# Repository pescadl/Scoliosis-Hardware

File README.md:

# Scoliosis-Hardware
Senior Design Project
with launchpad

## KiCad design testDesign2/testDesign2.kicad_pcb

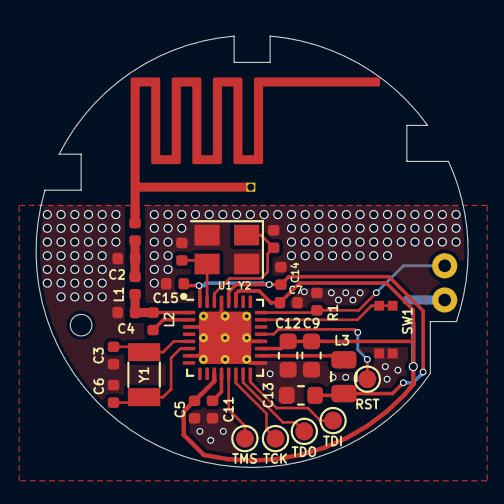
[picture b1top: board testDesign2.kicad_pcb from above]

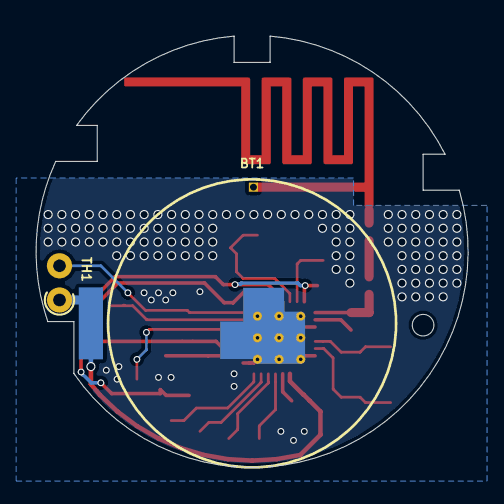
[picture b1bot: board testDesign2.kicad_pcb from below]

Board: 2 copper layers, 24.0 x 24.0 mm, 32 parts (2 on the bottom side), 20 nets.

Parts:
AE1: Antenna; TestDesign2_Antenna
BT1: Battery_Cell; BatteryHolder_Keystone_120_118_CR1616
C1, C3, C6: 12pF; C_0402_1005Metric
C2, C4: 1.2pF; C_0402_1005Metric
C5, C7, C14, C15: 100nF; C_0402_1005Metric
C8, C10: 9pF; C_0402_1005Metric
C9, C13: 10uF; C_0603_1608Metric
C11: 1uF; C_0402_1005Metric
C12: 100nF; C_0603_1608Metric
H1: MountingHole; MountingHole_1.2mm_M1
L1: 2nH; L_0402_1005Metric
L2: 15nH; L_0402_1005Metric
L3: 10uH; L_0805_2012Metric
R1: 51k; R_0402_1005Metric
RST: TP; TestPoint_Pad_D1.0mm
SW1: SW_Push; Switch_EVP-BB4A9B000
TCK: TP; TestPoint_Pad_D1.0mm
TDI: TP; TestPoint_Pad_D1.0mm
TDO: TP; TestPoint_Pad_D1.0mm
TH1: Thermistor; R_Axial_DIN0204_L3.6mm_D1.6mm_P1.90mm_Vertical
TMS: TP; TestPoint_Pad_D1.0mm
U1: CC2640R2FRSM; QFN-32-1EP_4x4mm_P0.4mm_EP2.9x2.9mm_ThermalVias
Y1: 32.768kHz; Crystal_SMD_3215-2Pin_3.2x1.5mm
Y2: 24MHz; Crystal_SMD_SeikoEpson_TSX3225-4Pin_3.2x2.5mm

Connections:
ADC0: R1.1, TH1.2, U1.24
Button: SW1.1, U1.23
DCDC_SW: L3.1, U1.18
GND: BT1.2, C2.2, C3.2, C4.2, C5.2, C6.2, C7.2, C8.2, C9.2, C10.2, C11.2, C12.2, C13.2, C14.2, C15.2, R1.2, SW1.2, U1.3, U1.7, U1.17, U1.20, U1.29, U1.33, Y2.2, Y2.4
unnamed: AE1.1, C1.1
unnamed: C1.2, C2.1, L1.1
unnamed: C3.1, U1.5, Y1.1
unnamed: C4.1, L1.2, L2.1, U1.1
unnamed: C6.1, U1.6, Y1.2
unnamed: C8.1, U1.31, Y2.3
unnamed: C10.1, U1.30, Y2.1
unnamed: C11.1, U1.12
unnamed: L2.2, U1.2
unnamed: TMS.1, U1.13
unnamed: TCK.1, U1.14
unnamed: TDO.1, U1.15
unnamed: TDI.1, U1.16
unnamed: RST.1, U1.21
VDDR: C13.1, C14.1, C15.1, L3.2, U1.28, U1.32
VDDS: BT1.1, C5.1, C7.1, C9.1, C12.1, TH1.1, U1.11, U1.19, U1.27

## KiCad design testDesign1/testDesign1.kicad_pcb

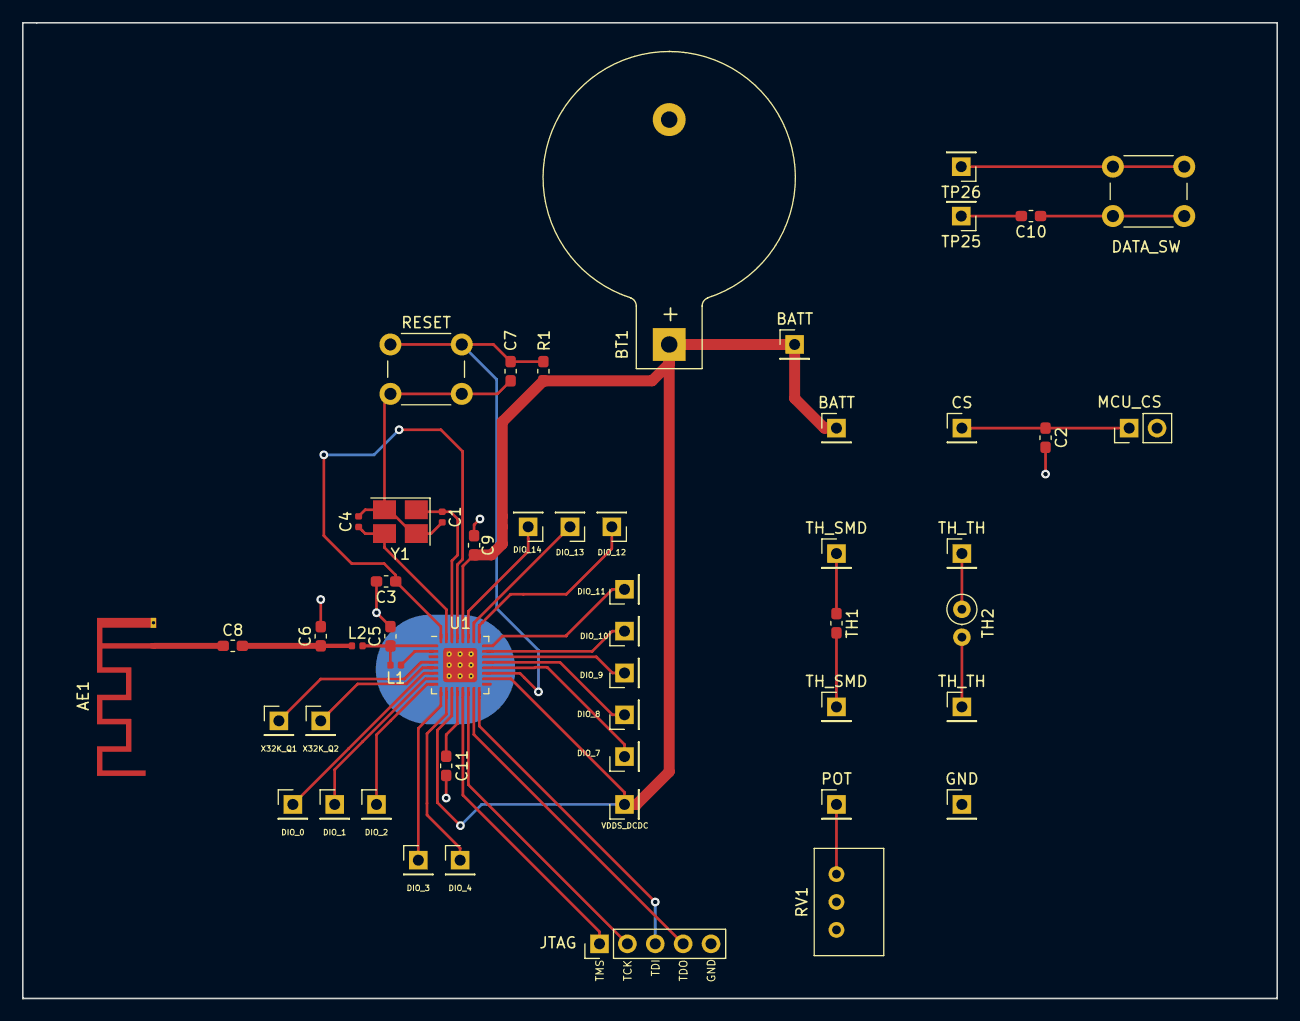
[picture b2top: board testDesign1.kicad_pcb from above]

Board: 2 copper layers, 114.3 x 88.9 mm, 52 parts (0 on the bottom side), 39 nets.

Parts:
AE1: Antenna; Texas_SWRA117D_2.4GHz_Left
BATT: TestPoint; PinHeader_1x01_P2.54mm_Vertical
BATT#2: TestPoint; PinHeader_1x01_P2.54mm_Vertical
BT1: Battery_Cell; BatteryHolder_Keystone_103_1x20mm
C1, C4: 9pF; C_0402_1005Metric
C2: 1nF; C_0603_1608Metric_Pad1.05x0.95mm_HandSolder
C3, C9: 10uF; C_0603_1608Metric_Pad1.05x0.95mm_HandSolder
C5, C6: 1.2pF; C_0603_1608Metric_Pad1.05x0.95mm_HandSolder
C7, C10: 100nF; C_0603_1608Metric_Pad1.05x0.95mm_HandSolder
C8: 12pF; C_0603_1608Metric_Pad1.05x0.95mm_HandSolder
C11: 1uF; C_0603_1608Metric_Pad1.05x0.95mm_HandSolder
CS: TestPoint; PinHeader_1x01_P2.54mm_Vertical
DATA_SW: SW_Push; SW_PUSH_6mm
DIO_0, DIO_1, DIO_2, DIO_3, DIO_4, DIO_7, DIO_8, DIO_9, DIO_10, DIO_11, DIO_12, DIO_13, DIO_14: TestPoint; PinHeader_1x01_P2.54mm_Vertical
GND: TestPoint; PinHeader_1x01_P2.54mm_Vertical
JTAG: Conn_01x05_Male; PinHeader_1x05_P2.54mm_Vertical
L1: 15nH; L_0402_1005Metric
L2: 2 nH; L_0402_1005Metric
MCU_CS: .; PinHeader_1x02_P2.54mm_Vertical
POT: TestPoint; PinHeader_1x01_P2.54mm_Vertical
R1: 100K; R_0603_1608Metric_Pad1.05x0.95mm_HandSolder
RESET: SW_Push; SW_PUSH_6mm
RV1: R_POT_TRIM_US; Potentiometer_Bourns_3299W_Vertical
TH1: Thermistor; R_0603_1608Metric_Pad1.05x0.95mm_HandSolder
TH2: Thermistor; R_Axial_DIN0207_L6.3mm_D2.5mm_P2.54mm_Vertical
TH_SMD: TestPoint; PinHeader_1x01_P2.54mm_Vertical
TH_SMD#2: TestPoint; PinHeader_1x01_P2.54mm_Vertical
TH_TH: TestPoint; PinHeader_1x01_P2.54mm_Vertical
TH_TH#2: TestPoint; PinHeader_1x01_P2.54mm_Vertical
TP25, TP26: TestPoint; PinHeader_1x01_P2.54mm_Vertical
U1: CC2640R2FRHB; QFN-32-1EP_5x5mm_P0.5mm_EP3.1x3.1mm_ThermalVias
VDDS_DCDC: TestPoint; PinHeader_1x01_P2.54mm_Vertical
X32K_Q1, X32K_Q2: TestPoint; PinHeader_1x01_P2.54mm_Vertical
Y1: Crystal_GND24; Crystal_SMD_SeikoEpson_TSX3225-4Pin_3.2x2.5mm_HandSoldering

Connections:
BATT: BATT.1, BATT#2.1, BT1.1, C9.1, R1.1, U1.11, U1.18, U1.28, VDDS_DCDC.1
GND: BT1.2, C1.2, C2.2, C3.2, C4.2, C5.2, C6.2, C7.2, C9.2, C11.2, GND.1, JTAG.5, RESET.2, RV1.2, RV1.3, U1.33, Y1.2, Y1.4
unnamed: AE1.1, C8.1
unnamed: C1.1, U1.30, Y1.1
unnamed: C2.1, CS.1, MCU_CS.1
unnamed: C3.1, U1.29, U1.32
unnamed: C4.1, U1.31, Y1.3
unnamed: C5.1, L1.2, L2.2, U1.1
unnamed: C6.1, C8.2, L2.1
unnamed: C7.1, R1.2, RESET.1, U1.19
unnamed: C10.1, DATA_SW.1
unnamed: C10.2, TP25.1
unnamed: C11.1, U1.12
unnamed: JTAG.1, U1.13
unnamed: JTAG.2, U1.14
unnamed: JTAG.3, U1.16
unnamed: JTAG.4, U1.15
unnamed: L1.1, U1.2
unnamed: POT.1, RV1.1
unnamed: DATA_SW.2, TP26.1
unnamed: TH1.1, TH_SMD.1
unnamed: TH1.2, TH_SMD#2.1
unnamed: TH2.1, TH_TH.1
unnamed: TH2.2, TH_TH#2.1
unnamed: DIO_12.1, U1.25
unnamed: DIO_13.1, U1.26
unnamed: DIO_14.1, U1.27
unnamed: DIO_11.1, U1.24
unnamed: DIO_10.1, U1.23
unnamed: DIO_9.1, U1.22
unnamed: DIO_8.1, U1.21
unnamed: U1.4, X32K_Q1.1
unnamed: DIO_7.1, U1.20
unnamed: U1.5, X32K_Q2.1
unnamed: DIO_0.1, U1.6
unnamed: DIO_1.1, U1.7
unnamed: DIO_2.1, U1.8
unnamed: DIO_4.1, U1.10
unnamed: DIO_3.1, U1.9

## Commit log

2018-11-18 First Commit. Got ADC sampling at 1 second interval using TI RTOS. Next need to add BLE
2018-12-02 Got BLE5 stuff to build. Now move on to figuring out the different threads in the BLE project to figure out how to add the ADC thread code
2019-01-30 am able to edit ble characteristic values and hex, but can only read in the first byte
2019-01-30 got Characteristic 1 to match Characteristic 5, meaning that the value can now hold 2 bytes instead of 1. We will use this to make this more than just 2 bytes, but many bytes
2019-02-02 created variable for changing length of values and updated to 7value for char 1
2019-02-06 only three characteristics
2019-02-06 changed BLE scanner name to Stellar Spine
2019-02-06 just the two chars now, no notify
2019-02-06 Started to move the adc stuff to TI RTOS. Will be done tomorrow.
2019-02-07 got ADC working with TI RTOS. added some stuff to .gitignore. Next will start working on base code for test board
2019-02-07 kicad files
2019-02-07 kicad files for test board
2019-02-13 two ADC tasks working at once
2019-03-08 clean biuld
2019-03-08 Removed Button1 stuff from projectzero.c file and it works.
2019-03-08 Changed Button0 to ButtonKeySelect enough so it works.
2019-03-08 Got ADC and Bluetooth working at the same time. Woohoo!
2019-03-08 Added software averaging for ADC.
2019-03-10 Added Battery Monitor to show for Mid-Project Demo. Will need to move out into it's own Callback function.
2019-03-25 Started on Second PCB
2019-03-25 Enclosure and PCB needs to be a CIRCLE
2019-03-26 Think PCB design is finished. Need to do last checkthrough.
2019-03-27 Added mounts to PCB and started enclosure.
2019-03-28 added some enclosure stuff
2019-04-01 Made a new version of the test enclosure w/o the insides done. Should screw in properly.
2019-04-01 launchpad working code
2019-04-02 has a data array for number of compliance data and compliance data
2019-04-03 commit everything for now. wanna go back to a previous commit
2019-04-04 only advertising after button, and then wont adv again until press button again
2019-04-06 sending test string
2019-04-08 getting rid of button1
2019-04-08 adding new service
2019-04-08 adding battery service and fixing some stuff with data storing
2019-04-08 currtime and data being sent
2019-04-08 removing button service
2019-04-08 removing changing data array
2019-04-08 idk what im doing
2019-04-08 correctly samples data
2019-04-08 added swi for timer
2019-04-09 added battery percentage
2019-04-10 added last Read Char
2019-04-10 comply in bits and added characterstic for #of data
2019-04-11 marisa forgot to change a char thingy but its fixed now
2019-04-12 Switching over to master
2019-04-19 Just Works method - untested
2019-04-29 saving before i make some breaking changes
2019-04-29 backup version almost complete. need to make small adjustments after receiving it
2019-04-29 no pairing, but 1400 threshold and deletes data after done
2019-04-30 finished top half of demo enclosure
2019-04-30 this code is working on our custom purple pcb
2019-04-30 minor bug
2019-05-01 started on purple pcb enclosure
2019-05-01 Fixed bug with lastread
2019-05-01 commit before stash
2019-05-01 Recovered correct testDesign files from old stash
2019-05-01 finished custom pcb enclosure w/ no thermistor hole
2019-05-01 o dear pls tell me im done
2019-06-07 removing unnecessary folders
2019-06-07 enclosure files
2019-06-07 restructuring
2019-06-08 uploaded some changes i didnt add from before
